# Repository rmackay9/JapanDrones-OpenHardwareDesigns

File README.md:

# JapanDrones Open Hardware Designs

Open hardware designs from [JapanDrones](https://japandrones.com) for ArduPilot based multicopters.

## Designs

| Design | Description | Status |
|---|---|---|
| [leds](leds/) | Round arm LEDs (under each motor) and a rectangular rear status LED, both 2x SK6812 RGB | Built (PCBWay, 2026) |
| [basic-carrier](basic-carrier/) | Carrier board for a CubePilot Cube with four AM32 ESCs, battery input and connectors (6 layers, 91 x 90 mm) | v0.11 pre-fab (v0.10 built by PCBWay, 2026) |

More designs (such as the smart battery case) will be added over time.

## Repository layout

Each design has its own folder containing (the BasicCarrier, a KiCad 10 design with its own review history, uses a slightly different layout described in its README):

- **KiCad source files** (`.kicad_pro`, `.kicad_sch`, `.kicad_pcb`), made with KiCad 9
- **`fab/`** manufacturing files: a zip of Gerbers + drill files, the BOM and the positions (pick and place) file
- **`3d/`** STEP model for mechanical CAD and an STL that GitHub can show in its 3D viewer
- **`docs/`** renders and photos
- **`README.md`** describing the design and how to order it

The STEP files and renders are generated from the KiCad files with [tools/export-3d.ps1](tools/export-3d.ps1) (run from the repo root on Windows with KiCad installed). STL files are converted from the STEP files.

## Licences

Each folder is under the licence below. A subfolder with its own `LICENSE` file is covered by that file, which overrides the top-level [LICENSE.txt](LICENSE.txt).

| Folder | Licence |
|---|---|
| [basic-carrier/](basic-carrier/) | GNU General Public License v3.0 ([basic-carrier/LICENSE](basic-carrier/LICENSE)), because its ESC section is derived from the [VimDrones AM32 ESC development board](https://github.com/VimDrones/AM32_esc_development_board) (GPL-3.0) |
| everything else (e.g. [leds/](leds/)) | [CERN Open Hardware Licence Version 2 - Strongly Reciprocal](LICENSE.txt) (`CERN-OHL-S-2.0`) |
| software (scripts and tools) | GNU General Public License v3, unless otherwise noted |

Copyright (c) 2026 JapanDrones

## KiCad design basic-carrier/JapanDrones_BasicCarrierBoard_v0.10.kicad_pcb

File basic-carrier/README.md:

# JapanDrones BasicCarrier

Carrier board for a CubePilot Cube (DF17 connectors) used on the JapanDrones aerial photography copter.

- KiCad 10 project: `JapanDrones_BasicCarrier.kicad_pro` (version-free name; the board revision is the `rev` field in the title block, shown on the silkscreen through `${REVISION}`).
- `fab/<version>/`: the exact Gerbers, BOM, positions and schematic PDF sent to the fab for that release.
- `tools/make_fab.py` makes `fab/<rev>/` for the revision in the title block (Gerbers, drill, zip, BOM, positions, IPC netlist, schematic PDF).
- Releases are git tags (`v0.10` = as built by PCBWay, Sep 2026).

## Known issues in v0.10 (fixed in v0.11 work)
- Battery connector wrong gender / polarity in BOM
- Fan powered from 5V instead of battery voltage
- ESC CAN_H / CAN_L swapped
- Buzzer quiet (piezo driven by low-side FET with no discharge path)

No external libraries are needed: every symbol and footprint is embedded in the schematic and PCB, the project libraries (`JapanDrones.kicad_sym`, `JapanDrones.pretty`) are referenced with `${KIPRJMOD}`, and the 3D models are KiCad 10 stock models (`${KICAD10_3DMODEL_DIR}`) or generated placeholders in `3dmodels/`.

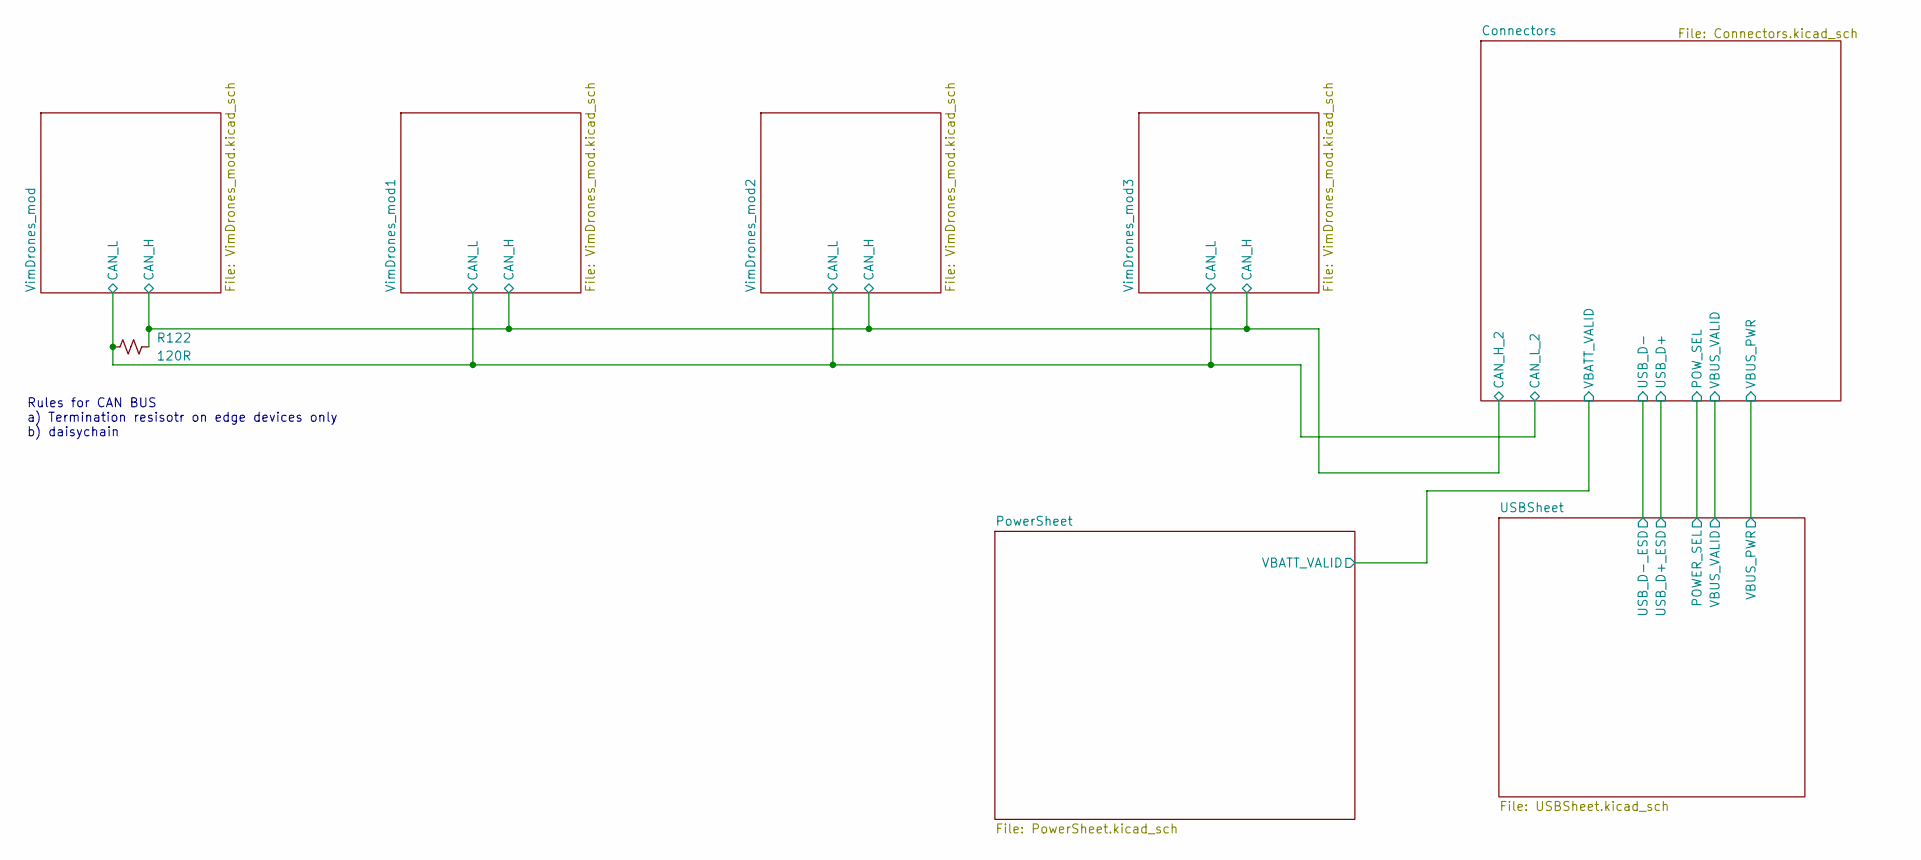
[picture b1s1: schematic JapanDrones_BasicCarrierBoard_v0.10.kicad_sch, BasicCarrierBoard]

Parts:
R122: 120R; R_1206_3216Metric; MPN 1206W4F1200T5E; LCSC C17909

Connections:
/Connectors/CAN_H_2: R122.2; also elsewhere on the board
/Connectors/CAN_L_2: R122.1; also elsewhere on the board

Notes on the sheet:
Rules for CAN BUS a) Termination resisotr on edge devices only b) daisychain

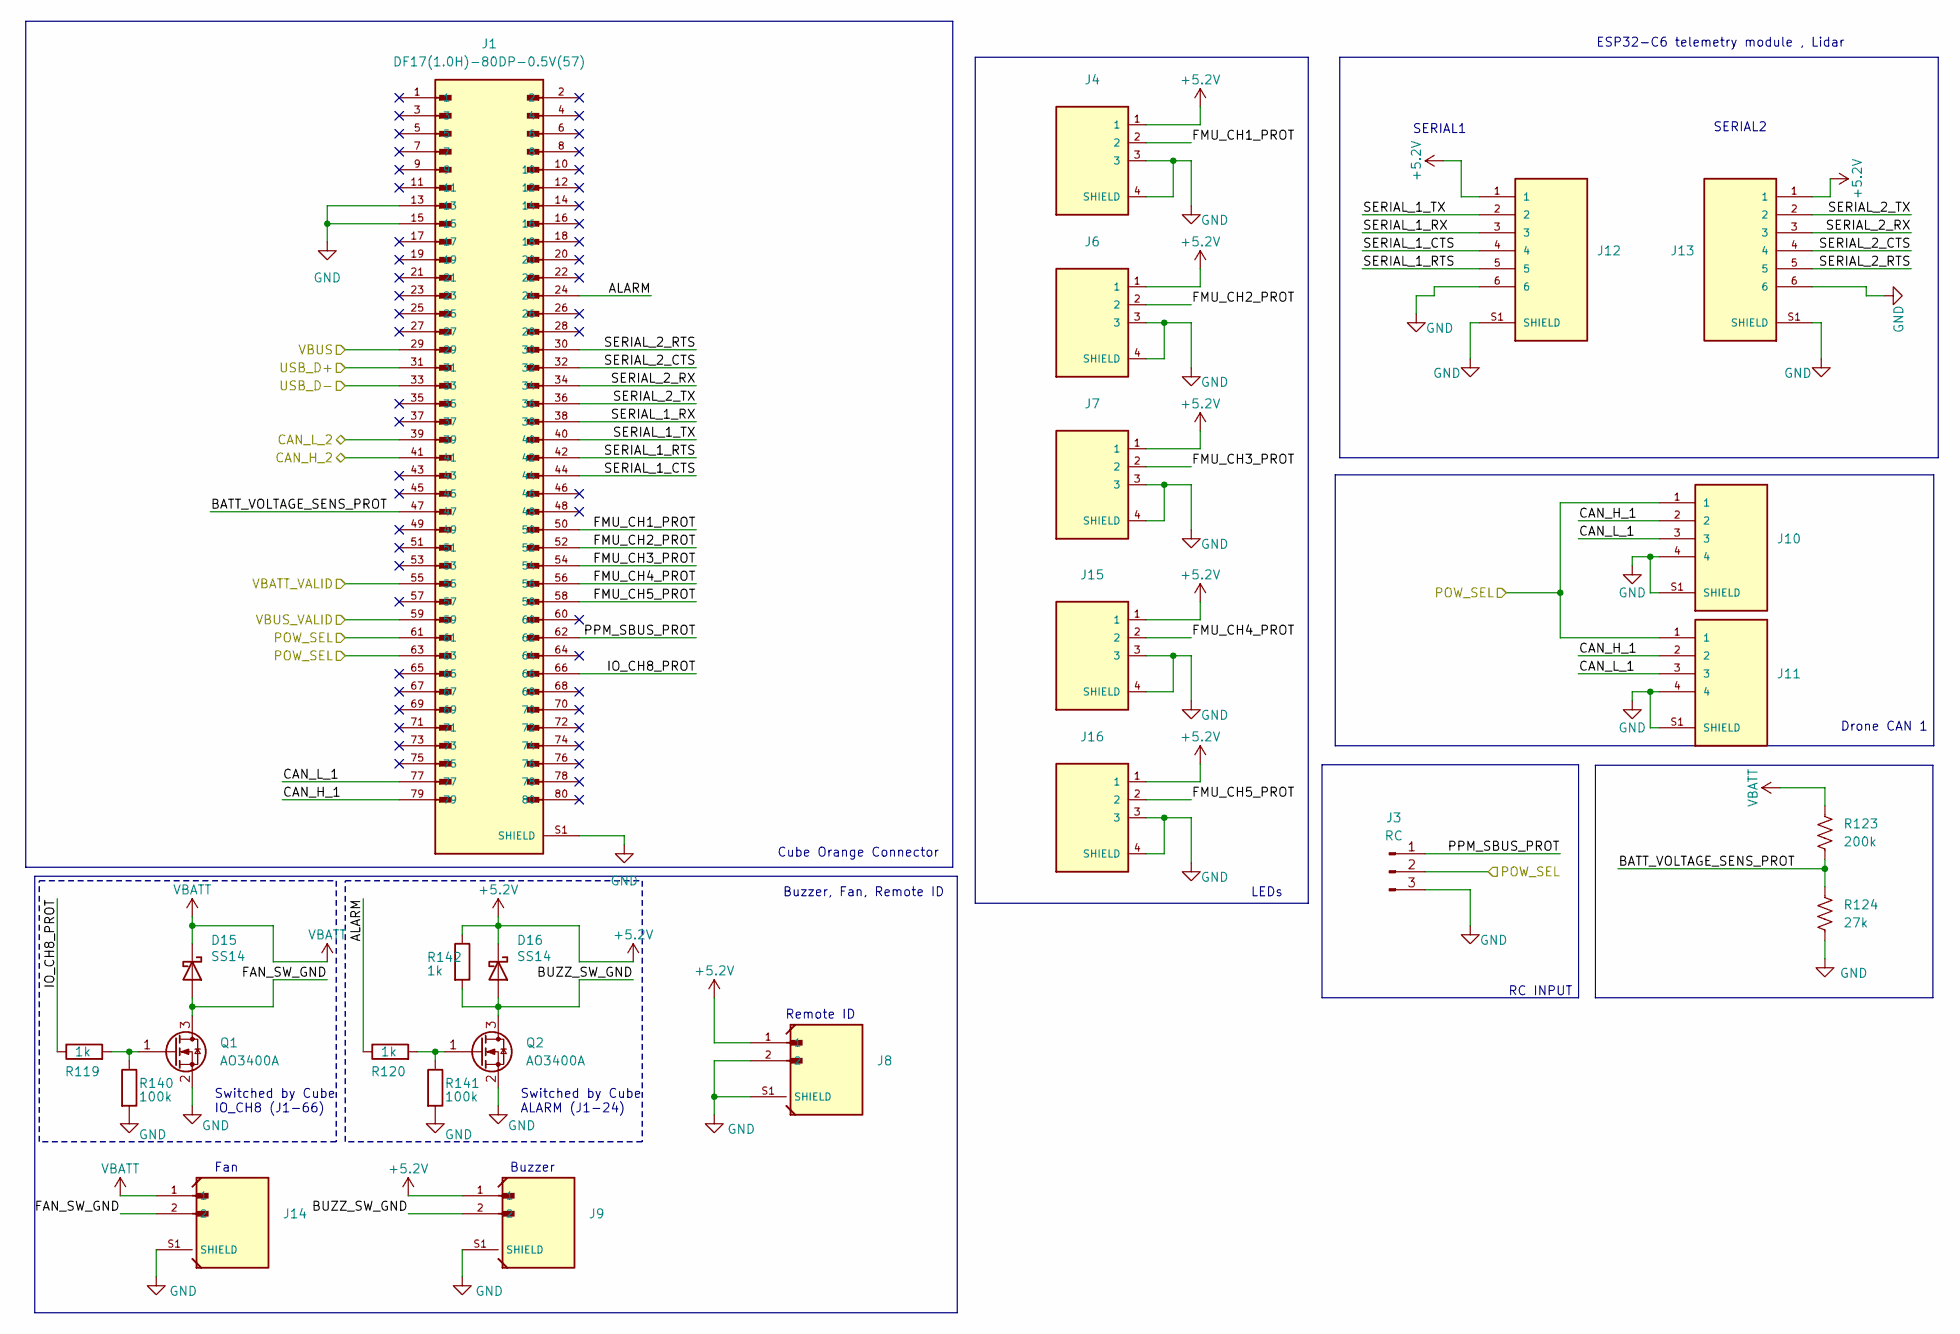
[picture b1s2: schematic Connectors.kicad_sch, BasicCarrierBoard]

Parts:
D15, D16: SS14; D_SOD-123FL; MPN SS14L; LCSC C190475
J1: DF17(1.0H)-80DP-0.5V(57); Hirose_DF17_1.0H-80DP-0.5V; MPN DF17(1.0H)-80DP-0.5V(57); LCSC C354837
J3: RC; PinHeader_1x03_P2.54mm_Vertical_SMD_Pin1Right; MPN 2.54-1*3PPin; LCSC C49257
J4, J6, J7, J15, J16: BM03B-GHS-TBT_LF__SN__N_; CONN_BM03B-GHS-TBT_LF__SN__N_; MPN BM03B-GHS-TBT(LF)(SN); LCSC C161691
J8, J9, J14: BM02B-GHS-TBT_LF__SN__N_; JST_BM02B-GHS-TBT_LF__SN__N_; MPN BM02B-GHS-TBT(LF)(SN); LCSC C161690
J10, J11: BM04B-GHS-TBT_LF__SN__N_; JST_BM04B-GHS-TBT_LF__SN__N_; PARTREV N/A; LCSC C161692
J12, J13: BM06B-GHS-TBT_LF__SN__N_; JST_BM06B-GHS-TBT_LF__SN__N_; PARTREV N/A; LCSC C189892
Q1, Q2: AO3400A; SOT-23; MPN AO3400A; LCSC C20917
R119, R120, R142: 1k; R_0805_2012Metric_Pad1.20x1.40mm_HandSolder; MPN 0805W8F1001T5E; LCSC C17513
R123: 200k; R_0603_1608Metric; MPN 0603WAF2003T5E; LCSC C25811
R124: 27k; R_0603_1608Metric; MPN 0603WAF2702T5E; LCSC C22967
R140, R141: 100k; R_0805_2012Metric_Pad1.20x1.40mm_HandSolder; MPN 0805W8F1003T5E; LCSC C17407

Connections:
+5.2V: D16.1 (K), J4.1, J6.1, J7.1, J8.1, J9.1, J12.1, J13.1, J15.1, J16.1, R142.1; also elsewhere on the board
/Connectors/ALARM: J1.24, R120.1
/Connectors/BATT_VOLTAGE_SENS_PROT: J1.47, R123.2, R124.1
/Connectors/BUZZ_SW_GND: D16.2 (A), J9.2, Q2.3 (D), R142.2
/Connectors/CAN_H_1: J1.79, J10.2, J11.2
/Connectors/CAN_H_2: J1.41; also elsewhere on the board
/Connectors/CAN_L_1: J1.77, J10.3, J11.3
/Connectors/CAN_L_2: J1.39; also elsewhere on the board
/Connectors/FAN_SW_GND: D15.2 (A), J14.2, Q1.3 (D)
/Connectors/FMU_CH1_PROT: J1.50, J4.2
/Connectors/FMU_CH2_PROT: J1.52, J6.2
/Connectors/FMU_CH3_PROT: J1.54, J7.2
/Connectors/FMU_CH4_PROT: J1.56, J15.2
/Connectors/FMU_CH5_PROT: J1.58, J16.2
/Connectors/IO_CH8_PROT: J1.66, R119.1
/Connectors/POW_SEL: J1.61, J1.63, J3.2, J10.1, J11.1; also elsewhere on the board
/Connectors/PPM_SBUS_PROT: J1.62, J3.1
/Connectors/SERIAL_1_CTS: J1.44, J12.4
/Connectors/SERIAL_1_RTS: J1.42, J12.5
/Connectors/SERIAL_1_RX: J1.38, J12.3
/Connectors/SERIAL_1_TX: J1.40, J12.2
/Connectors/SERIAL_2_CTS: J1.32, J13.4
/Connectors/SERIAL_2_RTS: J1.30, J13.5
/Connectors/SERIAL_2_RX: J1.34, J13.3
/Connectors/SERIAL_2_TX: J1.36, J13.2
/Connectors/USB_D+: J1.31; also elsewhere on the board
/Connectors/USB_D-: J1.33; also elsewhere on the board
/Connectors/VBATT_VALID: J1.55; also elsewhere on the board
/Connectors/VBUS_VALID: J1.59; also elsewhere on the board
/USBSheet/VBUS: J1.29; also elsewhere on the board
GND: J1.13, J1.15, J1.S1 (SHIELD), J1.S2 (SHIELD), J3.3, J4.3, J4.4 (SHIELD), J4.5 (SHIELD), J6.3, J6.4 (SHIELD), J6.5 (SHIELD), J7.3, J7.4 (SHIELD), J7.5 (SHIELD), J8.2, J8.S1 (SHIELD), J8.S2 (SHIELD), J9.S1 (SHIELD), J9.S2 (SHIELD), J10.4, J10.S1 (SHIELD), J10.S2 (SHIELD), J11.4, J11.S1 (SHIELD), J11.S2 (SHIELD), J12.6, J12.S1 (SHIELD), J12.S2 (SHIELD), J13.6, J13.S1 (SHIELD), J13.S2 (SHIELD), J14.S1 (SHIELD), J14.S2 (SHIELD), J15.3, J15.4 (SHIELD), J15.5 (SHIELD), J16.3, J16.4 (SHIELD), J16.5 (SHIELD), Q1.2 (S), Q2.2 (S), R124.2, R140.2, R141.2; also elsewhere on the board
unnamed: Q1.1 (G), R119.2, R140.1
unnamed: Q2.1 (G), R120.2, R141.1
VBATT: D15.1 (K), J14.1, R123.1; also elsewhere on the board

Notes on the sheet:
RC INPUT
ESP32-C6 telemetry module , Lidar
Fan
Buzzer
Switched by Cube IO_CH8 (J1-66)
Switched by Cube ALARM (J1-24)
Remote ID
Buzzer, Fan, Remote ID
SERIAL1
LEDs
Cube Orange Connector
Drone CAN 1
SERIAL2

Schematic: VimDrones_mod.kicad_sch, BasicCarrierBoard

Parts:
C1, C24: 10uF; C_0603_1608Metric; MPN CL10A106MA8NRNC; LCSC C96446
C2, C3, C4, C5, C6, C8, C15, C16, C23, C26: 100nF; C_0603_1608Metric; MPN CL10B104KB8NNNC; LCSC C1591
C7, C9, C12, C13, C14, C18, C19, C20: 10uF; C_1206_3216Metric; MPN CL31B106KBHNNNE; LCSC C89632
C21, C27, C28: 1uF; C_0603_1608Metric; MPN CL10B105KA8NNNC; LCSC C29936
D2, D5, D6: 1N5819WS; D_SOD-323; MPN 1N5819WS; LCSC C191023
J2: Motor Connectors; 1x03_conn_motor_JapanDrones; not fitted
J5: NC; 3P_ESC_OUT_50A_5.0mm_Pitch; not fitted
J28: BM06B-SRSS-TB_LF__SN_; JST_BM06B-SRSS-TB_LF__SN_; PARTREV N/A; LCSC C160392
MOTOR_MOUNT1: NC; 1404_4300kv_motor; not fitted
Q3, Q4, Q5, Q6, Q7, Q8: TPHR8504PL_L1Q; TRANS_TPHR8504PL_L1Q; PARTREV 3; LCSC C5331611
R1, R3, R4, R5, R7, R8, R10, R17, R18, R26, R29, R33, R34, R37, R38: 10k; R_0603_1608Metric; MPN 0603WAF1002T5E; LCSC C25804
R2, R6, R9: 1.2k; R_0603_1608Metric; MPN 0603WAF1201T5E; LCSC C22765
R16, R32, R35, R36, R39, R40: 10R; R_0603_1608Metric; MPN 0603WAF100JT5E; LCSC C22859
R19: 1k; R_0603_1608Metric; MPN 0603WAF1001T5E; LCSC C21190
R30: 22R; R_0603_1608Metric; MPN 0603WAF220JT5E; LCSC C23345
R31: 100k; R_0603_1608Metric; MPN 0603WAF1003T5E; LCSC C25803
RSHUNT2: 1mR 3W; R_2512_6332Metric_Pad1.40x3.35mm_HandSolder; MPN HoJLR2512-3W-1mR-1%; LCSC C2903470
U1: STM32L431KCUx; QFN-32-1EP_5x5mm_P0.5mm_EP3.45x3.45mm; MPN STM32L431KCU6TR; LCSC C2054968
U2: FD6288Q; QFN-24-1EP_4x4mm_P0.5mm_EP2.6x2.6mm_ThermalVias; MPN JSM6288Q; LCSC C19077370
U4: INA180B1; SOT-23-5; MPN INA180B1IDBVR; LCSC C544664
U7: TJA1051TK-3; HVSON-8-1EP_3x3mm_P0.65mm_EP1.6x2.4mm; MPN TJA1051TK/3/1J; LCSC C2875699
Y5: ASAAIG-24.000MHZ-K-C-S-T; XTAL_ASAAIG-24.000MHZ-K-C-S-T; PARTREV 10.28.2020; LCSC C1852571

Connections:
+3V3: C4.2, C5.2, C6.2, C8.2, C15.1, C26.1, J28.1, U1.1 (VDD), U1.5 (VDDA), U1.17 (VDD), U4.5 (V+), U7.5 (VIO), Y5.4 (VDD); also elsewhere on the board
+5.2V: C23.2, C24.1, U7.3 (VCC); also elsewhere on the board
+10V: C1.1, C3.1, D2.2 (A), D5.2 (A), D6.2 (A), U2.4 (VCC); also elsewhere on the board
/Connectors/CAN_H_2: U7.7 (CANH); also elsewhere on the board
/Connectors/CAN_L_2: U7.6 (CANL); also elsewhere on the board
/VimDrones_mod/ADC1_1N8_BATTERY_CURRENT: C16.1, R19.1, U1.9 (PA3)
/VimDrones_mod/ADC1_1N11_BATTERY_VOLTAGE: R29.2, R31.2, U1.12 (PA6)
/VimDrones_mod/CAN_RX: U1.21 (PA11), U7.4 (RXD)
/VimDrones_mod/CAN_TX: U1.22 (PA12), U7.1 (TXD)
/VimDrones_mod/COMP2_INP: R3.1, R7.1, R10.1, U1.27 (PB4)
/VimDrones_mod/COMP_INM_A: R1.1, R2.2, R3.2, U1.30 (PB7)
/VimDrones_mod/COMP_INM_B: R5.1, R6.2, R7.2, U1.11 (PA5)
/VimDrones_mod/COMP_INM_C: R8.1, R9.2, R10.2, U1.10 (PA4)
/VimDrones_mod/FD6288_HIN1: U1.20 (PA10), U2.22 (HIN1)
/VimDrones_mod/FD6288_HIN2: U1.19 (PA9), U2.23 (HIN2)
/VimDrones_mod/FD6288_HIN3: U1.18 (PA8), U2.24 (HIN3)
/VimDrones_mod/FD6288_HO1: R16.1, R17.2, U2.19 (HO1)
/VimDrones_mod/FD6288_HO2: R33.2, R35.1, U2.16 (HO2)
/VimDrones_mod/FD6288_HO3: R37.2, R39.1, U2.13 (HO3)
/VimDrones_mod/FD6288_LIN1: U1.15 (PB1), U2.1 (LIN1)
/VimDrones_mod/FD6288_LIN2: U1.14 (PB0), U2.2 (LIN2)
/VimDrones_mod/FD6288_LIN3: U1.13 (PA7), U2.3 (LIN3)
/VimDrones_mod/FD6288_LO1: R18.2, R32.1, U2.11 (LO1)
/VimDrones_mod/FD6288_LO2: R34.2, R36.1, U2.10 (LO2)
/VimDrones_mod/FD6288_LO3: R38.2, R40.1, U2.9 (LO3)
/VimDrones_mod/FD6288_VB1: C21.1, D2.1 (K), U2.20 (VB1)
/VimDrones_mod/FD6288_VB2: C27.1, D5.1 (K), U2.17 (VB2)
/VimDrones_mod/FD6288_VB3: C28.1, D6.1 (K), U2.14 (VB3)
/VimDrones_mod/FD6288_VS1: C21.2, J2.1, Q3.1, Q3.2, Q3.3, Q4.5, Q4.6, Q4.7, Q4.8, Q4.9, R1.2, R17.1, U2.18 (VS1)
/VimDrones_mod/FD6288_VS2: C27.2, J2.2, Q5.1, Q5.2, Q5.3, Q6.5, Q6.6, Q6.7, Q6.8, Q6.9, R5.2, R33.1, U2.15 (VS2)
/VimDrones_mod/FD6288_VS3: C28.2, J2.3, Q7.1, Q7.2, Q7.3, Q8.5, Q8.6, Q8.7, Q8.8, Q8.9, R8.2, R37.1, U2.12 (VS3)
/VimDrones_mod/HSE_IN: U1.6 (PA0), Y5.3 (OUTPUT)
/VimDrones_mod/MVDD: C7.1, C9.1, C12.1, C13.1, C14.1, C18.1, C19.1, C20.1, Q3.5, Q3.6, Q3.7, Q3.8, Q3.9, Q5.5, Q5.6, Q5.7, Q5.8, Q5.9, Q7.5, Q7.6, Q7.7, Q7.8, Q7.9, RSHUNT2.1, U4.3 (-)
/VimDrones_mod/ST_NRST: C2.2, J28.3, U1.4 (NRST)
/VimDrones_mod/ST_SWCLK: J28.5, U1.24 (PA14)
/VimDrones_mod/ST_SWDIO: J28.4, U1.23 (PA13)
/VimDrones_mod/USART1_TX: R30.1, U1.29 (PB6)
GND: C1.2, C2.1, C3.2, C4.1, C5.1, C6.1, C7.2, C8.1, C9.2, C12.2, C13.2, C14.2, C15.2, C16.2, C18.2, C19.2, C20.2, C23.1, C24.2, C26.2, J28.6, J28.S1 (SHIELD), J28.S2 (SHIELD), Q4.1, Q4.2, Q4.3, Q6.1, Q6.2, Q6.3, Q8.1, Q8.2, Q8.3, R2.1, R4.1, R6.1, R9.1, R18.1, R26.1, R29.1, R34.1, R38.1, U1.16 (VSS), U1.32 (VSS), U1.33 (VSS), U2.6 (COM), U2.25, U4.2 (GND), U7.2 (GND), U7.9 (GND), Y5.2 (GND); also elsewhere on the board
unnamed: J28.2, R30.2
unnamed: Q3.4, R16.2
unnamed: Q4.4, R32.2
unnamed: Q5.4, R35.2
unnamed: Q6.4, R36.2
unnamed: Q7.4, R39.2
unnamed: Q8.4, R40.2
unnamed: R19.2, U4.4
unnamed: R4.2, U1.31 (PH3)
unnamed: R26.2, U7.8 (S)
VBATT: R31.1, RSHUNT2.2, U4.1 (+); also elsewhere on the board

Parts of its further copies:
C41, C62, C64, C85, C87, C108: 10uF; C_0603_1608Metric; MPN CL10A106MA8NRNC; LCSC C96446
C42, C43, C44, C45, C46, C47, C51, C57, C60, C61, C65, C66, C67, C68, C69, C70, C74, C80, C83, C84, C88, C89, C90, C91, C92, C93, C97, C103, C106, C107: 100nF; C_0603_1608Metric; MPN CL10B104KB8NNNC; LCSC C1591
C48, C49, C50, C52, C54, C55, C56, C58, C71, C72, C73, C75, C77, C78, C79, C81, C94, C95, C96, C98, C100, C101, C102, C104: 10uF; C_1206_3216Metric; MPN CL31B106KBHNNNE; LCSC C89632
C53, C59, C63, C76, C82, C86, C99, C105, C109: 1uF; C_0603_1608Metric; MPN CL10B105KA8NNNC; LCSC C29936
D4, D7, D8, D9, D10, D11, D12, D13, D14: 1N5819WS; D_SOD-323; MPN 1N5819WS; LCSC C191023
J19, J22, J25: Motor Connectors; 1x03_conn_motor_JapanDrones; not fitted
J30, J31, J32: BM06B-SRSS-TB_LF__SN_; JST_BM06B-SRSS-TB_LF__SN_; PARTREV N/A; LCSC C160392
Q9, Q10, Q11, Q12, Q13, Q14, Q15, Q16, Q17, Q18, Q19, Q20, Q21, Q22, Q23, Q24, Q25, Q26: TPHR8504PL_L1Q; TRANS_TPHR8504PL_L1Q; PARTREV 3; LCSC C5331611
R12, R14, R15, R20, R22, R23, R25, R45, R49, R53, R55, R56, R59, R60, R63, R65, R67, R68, R69, R71, R72, R74, R75, R76, R80, R82, R83, R86, R87, R90, R92, R94, R95, R96, R98, R99, R101, R102, R103, R107, R109, R110, R113, R114, R117: 10k; R_0603_1608Metric; MPN 0603WAF1002T5E; LCSC C25804
R13, R21, R24, R66, R70, R73, R93, R97, R100: 1.2k; R_0603_1608Metric; MPN 0603WAF1201T5E; LCSC C22765
R50, R51, R57, R58, R61, R62, R77, R78, R84, R85, R88, R89, R104, R105, R111, R112, R115, R116: 10R; R_0603_1608Metric; MPN 0603WAF100JT5E; LCSC C22859
R52, R79, R106: 1k; R_0603_1608Metric; MPN 0603WAF1001T5E; LCSC C21190
R54, R81, R108: 100k; R_0603_1608Metric; MPN 0603WAF1003T5E; LCSC C25803
R64, R91, R118: 22R; R_0603_1608Metric; MPN 0603WAF220JT5E; LCSC C23345
RSHUNT3, RSHUNT4, RSHUNT5: 1mR 3W; R_2512_6332Metric_Pad1.40x3.35mm_HandSolder; MPN HoJLR2512-3W-1mR-1%; LCSC C2903470
U3, U12, U16: FD6288Q; QFN-24-1EP_4x4mm_P0.5mm_EP2.6x2.6mm_ThermalVias; MPN JSM6288Q; LCSC C19077370
U9, U13, U17: STM32L431KCUx; QFN-32-1EP_5x5mm_P0.5mm_EP3.45x3.45mm; MPN STM32L431KCU6TR; LCSC C2054968
U10, U14, U18: INA180B1; SOT-23-5; MPN INA180B1IDBVR; LCSC C544664
U11, U15, U19: TJA1051TK-3; HVSON-8-1EP_3x3mm_P0.65mm_EP1.6x2.4mm; MPN TJA1051TK/3/1J; LCSC C2875699
Y6, Y7, Y8: ASAAIG-24.000MHZ-K-C-S-T; XTAL_ASAAIG-24.000MHZ-K-C-S-T; PARTREV 10.28.2020; LCSC C1852571

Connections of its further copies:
+3V3: C44.2, C45.2, C46.2, C47.1, C57.2, C60.1, C67.2, C68.2, C69.2, C70.1, C80.2, C83.1, C90.2, C91.2, C92.2, C93.1, C103.2, C106.1, J30.1, J31.1, J32.1, U9.1 (VDD), U9.5 (VDDA), U9.17 (VDD), U10.5 (V+), U11.5 (VIO), U13.1 (VDD), U13.5 (VDDA), U13.17 (VDD), U14.5 (V+), U15.5 (VIO), U17.1 (VDD), U17.5 (VDDA), U17.17 (VDD), U18.5 (V+), U19.5 (VIO), Y6.4 (VDD), Y7.4 (VDD), Y8.4 (VDD); also elsewhere on the board
+5.2V: C61.2, C62.1, C84.2, C85.1, C107.2, C108.1, U11.3 (VCC), U15.3 (VCC), U19.3 (VCC); also elsewhere on the board
+10V: C41.1, C42.1, C64.1, C65.1, C87.1, C88.1, D4.2 (A), D7.2 (A), D8.2 (A), D9.2 (A), D10.2 (A), D11.2 (A), D12.2 (A), D13.2 (A), D14.2 (A), U3.4 (VCC), U12.4 (VCC), U16.4 (VCC); also elsewhere on the board
/Connectors/CAN_H_2: U11.7 (CANH), U15.7 (CANH), U19.7 (CANH); also elsewhere on the board
/Connectors/CAN_L_2: U11.6 (CANL), U15.6 (CANL), U19.6 (CANL); also elsewhere on the board
/VimDrones_mod1/ADC1_1N8_BATTERY_CURRENT: C51.1, R52.1, U9.9 (PA3)
/VimDrones_mod1/ADC1_1N11_BATTERY_VOLTAGE: R53.2, R54.2, U9.12 (PA6)
/VimDrones_mod1/CAN_RX: U9.21 (PA11), U11.4 (RXD)
/VimDrones_mod1/CAN_TX: U9.22 (PA12), U11.1 (TXD)
/VimDrones_mod1/COMP2_INP: R14.1, R22.1, R25.1, U9.27 (PB4)
/VimDrones_mod1/COMP_INM_A: R12.1, R13.2, R14.2, U9.30 (PB7)
/VimDrones_mod1/COMP_INM_B: R20.1, R21.2, R22.2, U9.11 (PA5)
/VimDrones_mod1/COMP_INM_C: R23.1, R24.2, R25.2, U9.10 (PA4)
/VimDrones_mod1/FD6288_HIN1: U3.22 (HIN1), U9.20 (PA10)
/VimDrones_mod1/FD6288_HIN2: U3.23 (HIN2), U9.19 (PA9)
/VimDrones_mod1/FD6288_HIN3: U3.24 (HIN3), U9.18 (PA8)
/VimDrones_mod1/FD6288_HO1: R45.2, R50.1, U3.19 (HO1)
/VimDrones_mod1/FD6288_HO2: R55.2, R57.1, U3.16 (HO2)
/VimDrones_mod1/FD6288_HO3: R59.2, R61.1, U3.13 (HO3)
/VimDrones_mod1/FD6288_LIN1: U3.1 (LIN1), U9.15 (PB1)
/VimDrones_mod1/FD6288_LIN2: U3.2 (LIN2), U9.14 (PB0)
/VimDrones_mod1/FD6288_LIN3: U3.3 (LIN3), U9.13 (PA7)
/VimDrones_mod1/FD6288_LO1: R49.2, R51.1, U3.11 (LO1)
/VimDrones_mod1/FD6288_LO2: R56.2, R58.1, U3.10 (LO2)
/VimDrones_mod1/FD6288_LO3: R60.2, R62.1, U3.9 (LO3)
/VimDrones_mod1/FD6288_VB1: C53.1, D4.1 (K), U3.20 (VB1)
/VimDrones_mod1/FD6288_VB2: C59.1, D7.1 (K), U3.17 (VB2)
/VimDrones_mod1/FD6288_VB3: C63.1, D8.1 (K), U3.14 (VB3)
/VimDrones_mod1/FD6288_VS1: C53.2, J19.1, Q9.1, Q9.2, Q9.3, Q10.5, Q10.6, Q10.7, Q10.8, Q10.9, R12.2, R45.1, U3.18 (VS1)
/VimDrones_mod1/FD6288_VS2: C59.2, J19.2, Q11.1, Q11.2, Q11.3, Q12.5, Q12.6, Q12.7, Q12.8, Q12.9, R20.2, R55.1, U3.15 (VS2)
/VimDrones_mod1/FD6288_VS3: C63.2, J19.3, Q13.1, Q13.2, Q13.3, Q14.5, Q14.6, Q14.7, Q14.8, Q14.9, R23.2, R59.1, U3.12 (VS3)
/VimDrones_mod1/HSE_IN: U9.6 (PA0), Y6.3 (OUTPUT)
/VimDrones_mod1/MVDD: C48.1, C49.1, C50.1, C52.1, C54.1, C55.1, C56.1, C58.1, Q9.5, Q9.6, Q9.7, Q9.8, Q9.9, Q11.5, Q11.6, Q11.7, Q11.8, Q11.9, Q13.5, Q13.6, Q13.7, Q13.8, Q13.9, RSHUNT3.1, U10.3 (-)
/VimDrones_mod1/ST_NRST: C43.2, J30.3, U9.4 (NRST)
/VimDrones_mod1/ST_SWCLK: J30.5, U9.24 (PA14)
/VimDrones_mod1/ST_SWDIO: J30.4, U9.23 (PA13)
/VimDrones_mod1/USART1_TX: R64.1, U9.29 (PB6)
/VimDrones_mod2/ADC1_1N8_BATTERY_CURRENT: C74.1, R79.1, U13.9 (PA3)
/VimDrones_mod2/ADC1_1N11_BATTERY_VOLTAGE: R80.2, R81.2, U13.12 (PA6)
/VimDrones_mod2/CAN_RX: U13.21 (PA11), U15.4 (RXD)
/VimDrones_mod2/CAN_TX: U13.22 (PA12), U15.1 (TXD)
/VimDrones_mod2/COMP2_INP: R67.1, R71.1, R74.1, U13.27 (PB4)
/VimDrones_mod2/COMP_INM_A: R65.1, R66.2, R67.2, U13.30 (PB7)
/VimDrones_mod2/COMP_INM_B: R69.1, R70.2, R71.2, U13.11 (PA5)
/VimDrones_mod2/COMP_INM_C: R72.1, R73.2, R74.2, U13.10 (PA4)
/VimDrones_mod2/FD6288_HIN1: U12.22 (HIN1), U13.20 (PA10)
/VimDrones_mod2/FD6288_HIN2: U12.23 (HIN2), U13.19 (PA9)
/VimDrones_mod2/FD6288_HIN3: U12.24 (HIN3), U13.18 (PA8)
/VimDrones_mod2/FD6288_HO1: R75.2, R77.1, U12.19 (HO1)
/VimDrones_mod2/FD6288_HO2: R82.2, R84.1, U12.16 (HO2)
/VimDrones_mod2/FD6288_HO3: R86.2, R88.1, U12.13 (HO3)
/VimDrones_mod2/FD6288_LIN1: U12.1 (LIN1), U13.15 (PB1)
/VimDrones_mod2/FD6288_LIN2: U12.2 (LIN2), U13.14 (PB0)
/VimDrones_mod2/FD6288_LIN3: U12.3 (LIN3), U13.13 (PA7)
/VimDrones_mod2/FD6288_LO1: R76.2, R78.1, U12.11 (LO1)
/VimDrones_mod2/FD6288_LO2: R83.2, R85.1, U12.10 (LO2)
/VimDrones_mod2/FD6288_LO3: R87.2, R89.1, U12.9 (LO3)
/VimDrones_mod2/FD6288_VB1: C76.1, D9.1 (K), U12.20 (VB1)
/VimDrones_mod2/FD6288_VB2: C82.1, D10.1 (K), U12.17 (VB2)
/VimDrones_mod2/FD6288_VB3: C86.1, D11.1 (K), U12.14 (VB3)
/VimDrones_mod2/FD6288_VS1: C76.2, J22.1, Q15.1, Q15.2, Q15.3, Q16.5, Q16.6, Q16.7, Q16.8, Q16.9, R65.2, R75.1, U12.18 (VS1)
/VimDrones_mod2/FD6288_VS2: C82.2, J22.2, Q17.1, Q17.2, Q17.3, Q18.5, Q18.6, Q18.7, Q18.8, Q18.9, R69.2, R82.1, U12.15 (VS2)
/VimDrones_mod2/FD6288_VS3: C86.2, J22.3, Q19.1, Q19.2, Q19.3, Q20.5, Q20.6, Q20.7, Q20.8, Q20.9, R72.2, R86.1, U12.12 (VS3)
/VimDrones_mod2/HSE_IN: U13.6 (PA0), Y7.3 (OUTPUT)
/VimDrones_mod2/MVDD: C71.1, C72.1, C73.1, C75.1, C77.1, C78.1, C79.1, C81.1, Q15.5, Q15.6, Q15.7, Q15.8, Q15.9, Q17.5, Q17.6, Q17.7, Q17.8, Q17.9, Q19.5, Q19.6, Q19.7, Q19.8, Q19.9, RSHUNT4.1, U14.3 (-)
/VimDrones_mod2/ST_NRST: C66.2, J31.3, U13.4 (NRST)
/VimDrones_mod2/ST_SWCLK: J31.5, U13.24 (PA14)
/VimDrones_mod2/ST_SWDIO: J31.4, U13.23 (PA13)
/VimDrones_mod2/USART1_TX: R91.1, U13.29 (PB6)
/VimDrones_mod3/ADC1_1N8_BATTERY_CURRENT: C97.1, R106.1, U17.9 (PA3)
/VimDrones_mod3/ADC1_1N11_BATTERY_VOLTAGE: R107.2, R108.2, U17.12 (PA6)
/VimDrones_mod3/CAN_RX: U17.21 (PA11), U19.4 (RXD)
/VimDrones_mod3/CAN_TX: U17.22 (PA12), U19.1 (TXD)
/VimDrones_mod3/COMP2_INP: R94.1, R98.1, R101.1, U17.27 (PB4)
/VimDrones_mod3/COMP_INM_A: R92.1, R93.2, R94.2, U17.30 (PB7)
/VimDrones_mod3/COMP_INM_B: R96.1, R97.2, R98.2, U17.11 (PA5)
/VimDrones_mod3/COMP_INM_C: R99.1, R100.2, R101.2, U17.10 (PA4)
/VimDrones_mod3/FD6288_HIN1: U16.22 (HIN1), U17.20 (PA10)
/VimDrones_mod3/FD6288_HIN2: U16.23 (HIN2), U17.19 (PA9)
/VimDrones_mod3/FD6288_HIN3: U16.24 (HIN3), U17.18 (PA8)
/VimDrones_mod3/FD6288_HO1: R102.2, R104.1, U16.19 (HO1)
/VimDrones_mod3/FD6288_HO2: R109.2, R111.1, U16.16 (HO2)
/VimDrones_mod3/FD6288_HO3: R113.2, R115.1, U16.13 (HO3)
/VimDrones_mod3/FD6288_LIN1: U16.1 (LIN1), U17.15 (PB1)
/VimDrones_mod3/FD6288_LIN2: U16.2 (LIN2), U17.14 (PB0)
/VimDrones_mod3/FD6288_LIN3: U16.3 (LIN3), U17.13 (PA7)
/VimDrones_mod3/FD6288_LO1: R103.2, R105.1, U16.11 (LO1)
/VimDrones_mod3/FD6288_LO2: R110.2, R112.1, U16.10 (LO2)
/VimDrones_mod3/FD6288_LO3: R114.2, R116.1, U16.9 (LO3)
/VimDrones_mod3/FD6288_VB1: C99.1, D12.1 (K), U16.20 (VB1)
/VimDrones_mod3/FD6288_VB2: C105.1, D13.1 (K), U16.17 (VB2)
/VimDrones_mod3/FD6288_VB3: C109.1, D14.1 (K), U16.14 (VB3)
/VimDrones_mod3/FD6288_VS1: C99.2, J25.1, Q21.1, Q21.2, Q21.3, Q22.5, Q22.6, Q22.7, Q22.8, Q22.9, R92.2, R102.1, U16.18 (VS1)
/VimDrones_mod3/FD6288_VS2: C105.2, J25.2, Q23.1, Q23.2, Q23.3, Q24.5, Q24.6, Q24.7, Q24.8, Q24.9, R96.2, R109.1, U16.15 (VS2)
/VimDrones_mod3/FD6288_VS3: C109.2, J25.3, Q25.1, Q25.2, Q25.3, Q26.5, Q26.6, Q26.7, Q26.8, Q26.9, R99.2, R113.1, U16.12 (VS3)
/VimDrones_mod3/HSE_IN: U17.6 (PA0), Y8.3 (OUTPUT)
/VimDrones_mod3/MVDD: C94.1, C95.1, C96.1, C98.1, C100.1, C101.1, C102.1, C104.1, Q21.5, Q21.6, Q21.7, Q21.8, Q21.9, Q23.5, Q23.6, Q23.7, Q23.8, Q23.9, Q25.5, Q25.6, Q25.7, Q25.8, Q25.9, RSHUNT5.1, U18.3 (-)
/VimDrones_mod3/ST_NRST: C89.2, J32.3, U17.4 (NRST)
/VimDrones_mod3/ST_SWCLK: J32.5, U17.24 (PA14)
/VimDrones_mod3/ST_SWDIO: J32.4, U17.23 (PA13)
/VimDrones_mod3/USART1_TX: R118.1, U17.29 (PB6)
GND: C41.2, C42.2, C43.1, C44.1, C45.1, C46.1, C47.2, C48.2, C49.2, C50.2, C51.2, C52.2, C54.2, C55.2, C56.2, C57.1, C58.2, C60.2, C61.1, C62.2, C64.2, C65.2, C66.1, C67.1, C68.1, C69.1, C70.2, C71.2, C72.2, C73.2, C74.2, C75.2, C77.2, C78.2, C79.2, C80.1, C81.2, C83.2, C84.1, C85.2, C87.2, C88.2, C89.1, C90.1, C91.1, C92.1, C93.2, C94.2, C95.2, C96.2, C97.2, C98.2, C100.2, C101.2, C102.2, C103.1, C104.2, C106.2, C107.1, C108.2, J30.6, J30.S1 (SHIELD), J30.S2 (SHIELD), J31.6, J31.S1 (SHIELD), J31.S2 (SHIELD), J32.6, J32.S1 (SHIELD), J32.S2 (SHIELD), Q10.1, Q10.2, Q10.3, Q12.1, Q12.2, Q12.3, Q14.1, Q14.2, Q14.3, Q16.1, Q16.2, Q16.3, Q18.1, Q18.2, Q18.3, Q20.1, Q20.2, Q20.3, Q22.1, Q22.2, Q22.3, Q24.1, Q24.2, Q24.3, Q26.1, Q26.2, Q26.3, R13.1, R15.1, R21.1, R24.1, R49.1, R53.1, R56.1, R60.1, R63.1, R66.1, R68.1, R70.1, R73.1, R76.1, R80.1, R83.1, R87.1, R90.1, R93.1, R95.1, R97.1, R100.1, R103.1, R107.1, R110.1, R114.1, R117.1, U3.6 (COM), U3.25, U9.16 (VSS), U9.32 (VSS), U9.33 (VSS), U10.2 (GND), U11.2 (GND), U11.9 (GND), U12.6 (COM), U12.25, U13.16 (VSS), U13.32 (VSS), U13.33 (VSS), U14.2 (GND), U15.2 (GND), U15.9 (GND), U16.6 (COM), U16.25, U17.16 (VSS), U17.32 (VSS), U17.33 (VSS), U18.2 (GND), U19.2 (GND), U19.9 (GND), Y6.2 (GND), Y7.2 (GND), Y8.2 (GND); also elsewhere on the board
unnamed: J30.2, R64.2
unnamed: J31.2, R91.2
unnamed: J32.2, R118.2
unnamed: Q9.4, R50.2
unnamed: Q10.4, R51.2
unnamed: Q11.4, R57.2
unnamed: Q12.4, R58.2
unnamed: Q13.4, R61.2
unnamed: Q14.4, R62.2
unnamed: Q15.4, R77.2
unnamed: Q16.4, R78.2
unnamed: Q17.4, R84.2
unnamed: Q18.4, R85.2
unnamed: Q19.4, R88.2
unnamed: Q20.4, R89.2
unnamed: Q21.4, R104.2
unnamed: Q22.4, R105.2
unnamed: Q23.4, R111.2
unnamed: Q24.4, R112.2
unnamed: Q25.4, R115.2
unnamed: Q26.4, R116.2
unnamed: R52.2, U10.4
unnamed: R79.2, U14.4
unnamed: R106.2, U18.4
unnamed: R15.2, U9.31 (PH3)
unnamed: R63.2, U11.8 (S)
unnamed: R68.2, U13.31 (PH3)
unnamed: R90.2, U15.8 (S)
unnamed: R95.2, U17.31 (PH3)
unnamed: R117.2, U19.8 (S)
VBATT: R54.1, R81.1, R108.1, RSHUNT3.2, RSHUNT4.2, RSHUNT5.2, U10.1 (+), U14.1 (+), U18.1 (+); also elsewhere on the board

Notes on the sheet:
DEBUG / SIGNAL / TELEM INTERFACE
Structural Matching (test points slot)
NOW we will run paths form main battery directly on PCB
BOX KEPT for Structural Matching (neo-pixel slot)
only one set of pads
FD6288 DRIVE
VOLTAGE & CURRENT
REVERSED INTERFACE
PHASE A
BEMF
BATTERY PAD
Reset Switch deleted in Mod
2,3,7,8,25,26,28 : ARE NC
PHASE C
TRACE PATH VERY IMPORTANT ON PCB LAYOUT SIDE
(GAIN=20)
MOTOR PAD
PHASE B
CAN INTERFACE
WE had 5V and 3.3V regulators here but now we will get them from our common regulators

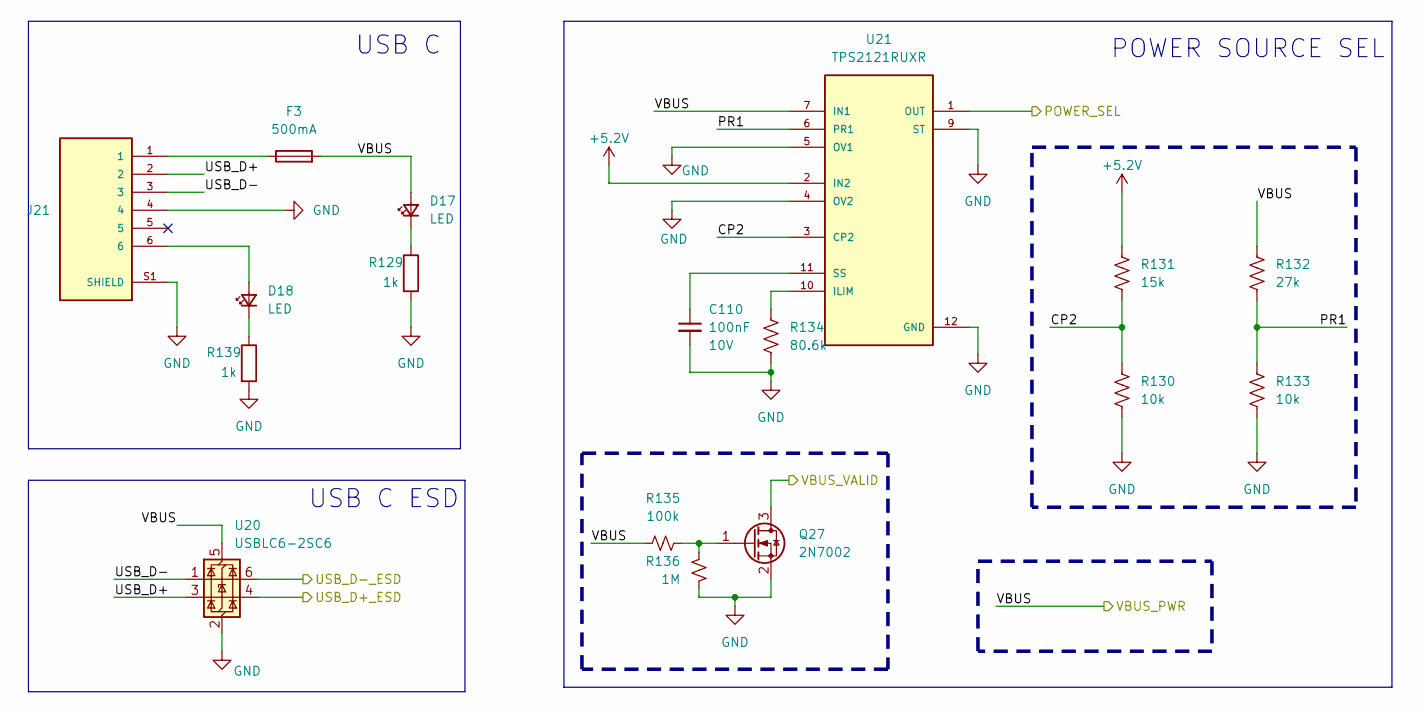
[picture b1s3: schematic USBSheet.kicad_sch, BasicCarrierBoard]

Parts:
C110: 100nF; C_0603_1608Metric; Voltage 10V; Tolerance 100%; MPN CL10B104KB8NNNC; LCSC C1591
D17, D18: LED; LED_1206_3216Metric_Pad1.42x1.75mm_HandSolder; MPN KT-1206R; LCSC C49018
F3: 500mA; Fuse_0805_2012Metric_Pad1.15x1.40mm_HandSolder; MPN ASMD0805-050; LCSC C135329
J21: BM06B-GHS-TBT_LF__SN__N_; JST_BM06B-GHS-TBT_LF__SN__N_; PARTREV N/A; LCSC C189892
Q27: 2N7002; SOT-23; MPN 2N7002; LCSC C8545
R129, R139: 1k; R_0805_2012Metric_Pad1.20x1.40mm_HandSolder; MPN 0805W8F1001T5E; LCSC C17513
R130, R133: 10k; R_0603_1608Metric; MPN 0603WAF1002T5E; LCSC C25804
R131: 15k; R_0603_1608Metric; MPN 0603WAF1502T5E; LCSC C22809
R132: 27k; R_0603_1608Metric; MPN 0603WAF2702T5E; LCSC C22967
R134: 80.6k; R_0603_1608Metric; MPN 0603WAF8062T5E; LCSC C23249
R135: 100k; R_0402_1005Metric; MPN 0402WGF1003TCE; LCSC C25741
R136: 1M; R_0402_1005Metric; MPN 0402WGF1004TCE; LCSC C26083
U20: USBLC6-2SC6; SOT-23-6; MPN USBLC6-2SC6; LCSC C7519
U21: TPS2121RUXR; IC_TPS2121RUXR; MPN TPS2121RUXR; LCSC C485916

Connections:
+5.2V: R131.1, U21.2 (IN2), U21.2_1 (IN2); also elsewhere on the board
/Connectors/POW_SEL: U21.1 (OUT), U21.1_1 (OUT), U21.8 (OUT), U21.8_1 (OUT); also elsewhere on the board
/Connectors/USB_D+: U20.4 (I/O2); also elsewhere on the board
/Connectors/USB_D-: U20.6 (I/O1); also elsewhere on the board
/Connectors/VBUS_VALID: Q27.3 (D); also elsewhere on the board
/USBSheet/CP2: R130.1, R131.2, U21.3 (CP2)
/USBSheet/PR1: R132.2, R133.1, U21.6 (PR1)
/USBSheet/USB_D+: J21.2, U20.3 (I/O2)
/USBSheet/USB_D-: J21.3, U20.1 (I/O1)
/USBSheet/VBUS: D17.2 (A), F3.2, R132.1, R135.1, U20.5 (VBUS), U21.7 (IN1), U21.7_1 (IN1); also elsewhere on the board
GND: C110.2, J21.4, J21.S1 (SHIELD), J21.S2 (SHIELD), Q27.2 (S), R129.2, R130.2, R133.2, R134.2, R136.1, R139.2, U20.2 (GND), U21.4 (OV2), U21.5 (OV1), U21.9 (ST), U21.12 (GND); also elsewhere on the board
unnamed: D17.1 (K), R129.1
unnamed: D18.2 (A), J21.6
unnamed: D18.1 (K), R139.1
unnamed: F3.1, J21.1
unnamed 208: Q27.1 (G), R135.2, R136.2; also elsewhere on the board
unnamed: R134.1, U21.10 (ILIM)
unnamed: C110.1, U21.11 (SS)

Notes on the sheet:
USB C
USB C ESD
POWER SOURCE SEL
